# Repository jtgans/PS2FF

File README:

This is a simple board to handle exposing of the modern IBM PS/2 media sense
floppy disk controller such that it can be faked out on the controller side.

IOW, FlashFloppy (and by extension Gotek flash-based floppy drives) currently
cannot handle the advanced media sensing back to the PS/2 host controller. This
adapter exposes those media sense pins so that we can "fake" the media report
type to the host controller.

The board has been fabbed via OshPark, and is available here:
https://oshpark.com/shared_projects/WMa6Bw9U

The BoM was picked from DigiKey parts, and is available here:
http://www.digikey.com/short/2n20v9zv

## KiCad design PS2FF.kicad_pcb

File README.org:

* PS/2 to FlashFloppy Media Sense Adapter

NOTE: This is still under development and does not work. Please don't assemble until revision C.

[[PS2FF.png]]

This is a simple board to handle exposing of the modern IBM PS/2 media sense
floppy disk controller such that it can be faked out on the controller side.

IOW, FlashFloppy (and by extension Gotek flash-based floppy drives) currently
cannot handle the advanced media sensing back to the PS/2 host controller. This
adapter exposes those media sense pins so that we can "fake" the media report
type to the host controller.

The board has been fabbed via OshPark, and is available here:
https://oshpark.com/shared_projects/C5xEJw8V

The BoM was picked from DigiKey parts, and is available here:
https://www.digikey.com/short/q1v7w5mt

[[PS2FF_board_art.png]]

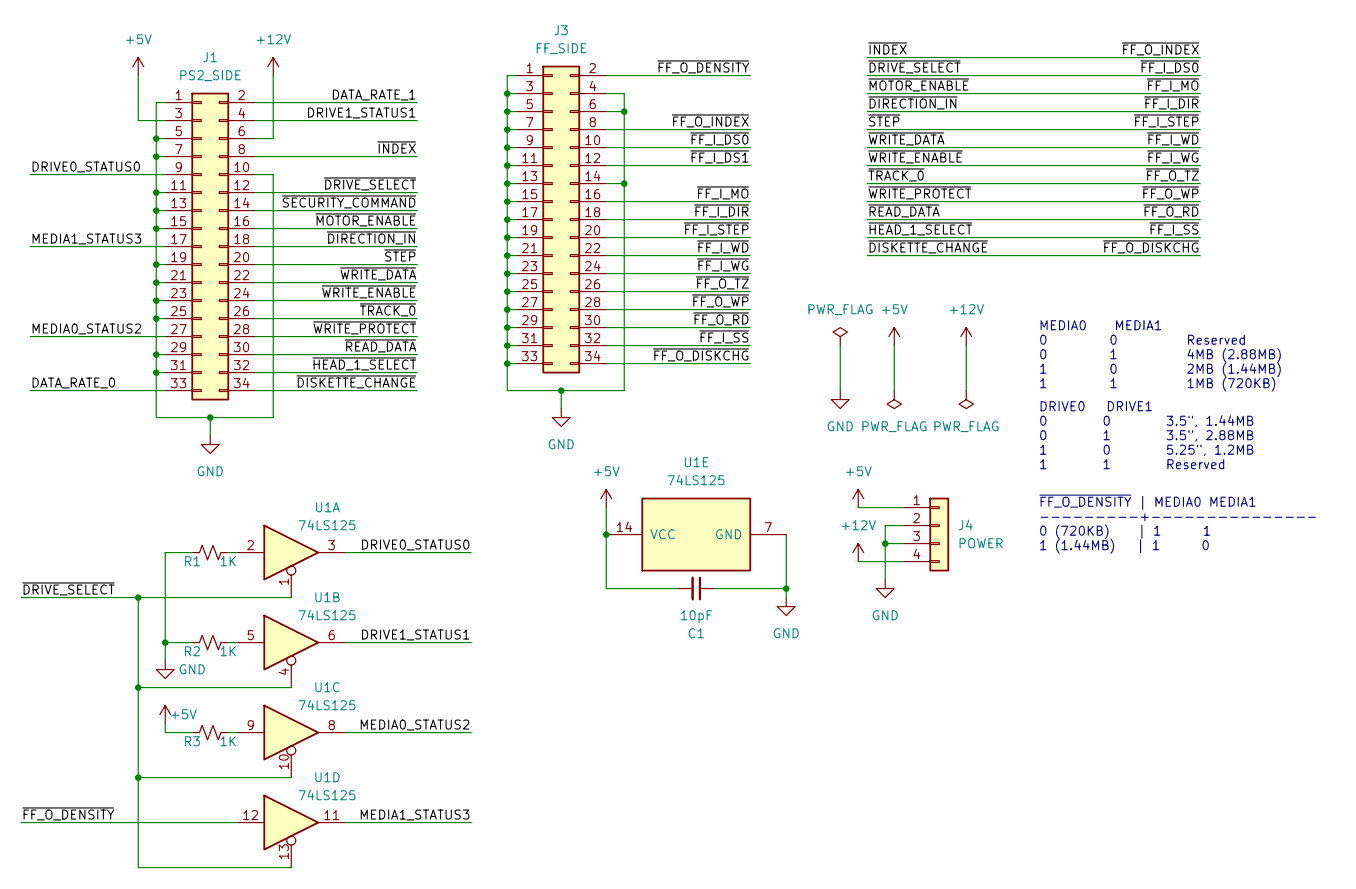
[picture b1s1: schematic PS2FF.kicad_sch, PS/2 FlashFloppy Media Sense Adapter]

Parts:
C1: 10pF; C_0805_2012Metric_Pad1.18x1.45mm_HandSolder
J1: PS2_SIDE; IDC-Header_2x17_P2.54mm_Horizontal
J3: FF_SIDE; IDC-Header_2x17_P2.54mm_Horizontal
J4: POWER; PinHeader_1x04_P2.54mm_Vertical
R1, R2, R3: 1K; R_0805_2012Metric
U1: 74LS125; SOIC-14_3.9x8.7mm_P1.27mm

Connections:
+5V: C1.2, J1.3, J4.1, R3.2, U1.14 (VCC)
+12V: J1.6, J4.4
/DATA_RATE_0: J1.33
/DATA_RATE_1: J1.2
/DRIVE0_STATUS0: J1.9, U1.3
/DRIVE1_STATUS1: J1.4, U1.6
/MEDIA0_STATUS2: J1.27, U1.8
/MEDIA1_STATUS3: J1.17, U1.11
/~DIRECTION_IN: J1.18, J3.18
/~DISKETTE_CHANGE: J1.34, J3.34
/~DRIVE_SELECT: J1.12, J3.10, U1.1, U1.4, U1.10, U1.13
/~FF_I_DS1: J3.12
/~FF_I_MO: J1.16, J3.16
/~FF_I_SS: J1.32, J3.32
/~FF_I_STEP: J1.20, J3.20
/~FF_I_WD: J1.22, J3.22
/~FF_I_WG: J1.24, J3.24
/~FF_O_DENSITY: J3.2, U1.12
/~FF_O_INDEX: J1.8, J3.8
/~FF_O_RD: J1.30, J3.30
/~FF_O_TZ: J1.26, J3.26
/~FF_O_WP: J1.28, J3.28
/~SECURITY_COMMAND: J1.14
GND: C1.1, J1.1, J1.5, J1.7, J1.10, J1.11, J1.13, J1.15, J1.19, J1.21, J1.23, J1.25, J1.29, J1.31, J3.1, J3.3, J3.4, J3.5, J3.6, J3.7, J3.9, J3.11, J3.13, J3.14, J3.15, J3.17, J3.19, J3.21, J3.23, J3.25, J3.27, J3.29, J3.31, J3.33, J4.2, J4.3, R1.2, R2.2, U1.7 (GND)
unnamed: R1.1, U1.2
unnamed: R2.1, U1.5
unnamed: R3.1, U1.9

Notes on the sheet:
DRIVE0 DRIVE1 0 0 3.5", 1.44MB 0 1 3.5", 2.88MB 1 0 5.25", 1.2MB 1 1 Reserved
MEDIA0 MEDIA1 0 0 Reserved 0 1 4MB (2.88MB) 1 0 2MB (1.44MB) 1 1 1MB (720KB)
~{FF_O_DENSITY} | MEDIA0 MEDIA1 ---------+--------------- 0 (720KB) | 1 1 1 (1.44MB) | 1 0

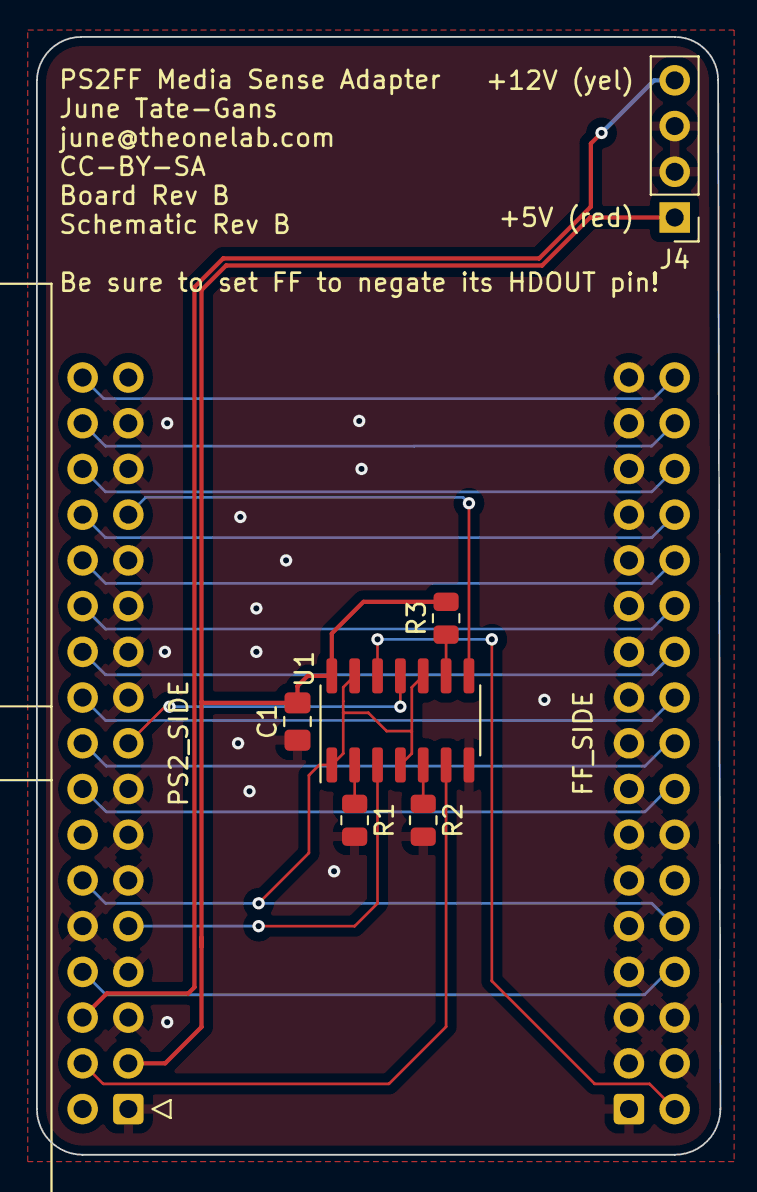
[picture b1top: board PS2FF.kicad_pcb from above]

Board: 2 copper layers, 38.0 x 62.1 mm, 8 parts (1 on the bottom side), 23 nets.

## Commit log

2022-09-29 first commit: Import revision A of the schematic and board
2022-09-29 readme: Add in a base-level readme file.
2022-09-29 readme: Add in oshpark and digikey links
2022-09-29 readme: Add in a board rendering
2022-09-29 readme: add in some board art images
2022-09-30 Fix up some DRC errors in the schematic
2022-09-30 Bump the board rev since new changes
2022-10-03 automate things: Swap to using a buffer to automate
    - Use a simple buffer to drive outputs to the host side.
    - Wire in FF_O_DENSITY to the appropriate pin via the buffers.
    Note: this requires FF to be set to invert this output!
2022-10-03 silks: Add a note about the hdout pin
2022-10-03 writing: Actually wire up the HDOUT pin from the FF side
    Update the links with the rev B schematic/PCB for fab.

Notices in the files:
PS2FF.kicad_pcb:
CC-BY-SA
